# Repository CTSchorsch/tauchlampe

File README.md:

# tauchlampe

10W LED Tanklampe mit Goodmanhandle

Version 4.2
- neues PCB, einseitig, liegt direkt auf der LED-Aufnahme auf, JST Stecker für Taster und Power
- Abdeckung für PCB
- LED-Aufnahme für Produktion vereinfacht
- Deckel für Akkufach: 2 Bananenbuchsen zum laden, Durchführung für JST Kabel

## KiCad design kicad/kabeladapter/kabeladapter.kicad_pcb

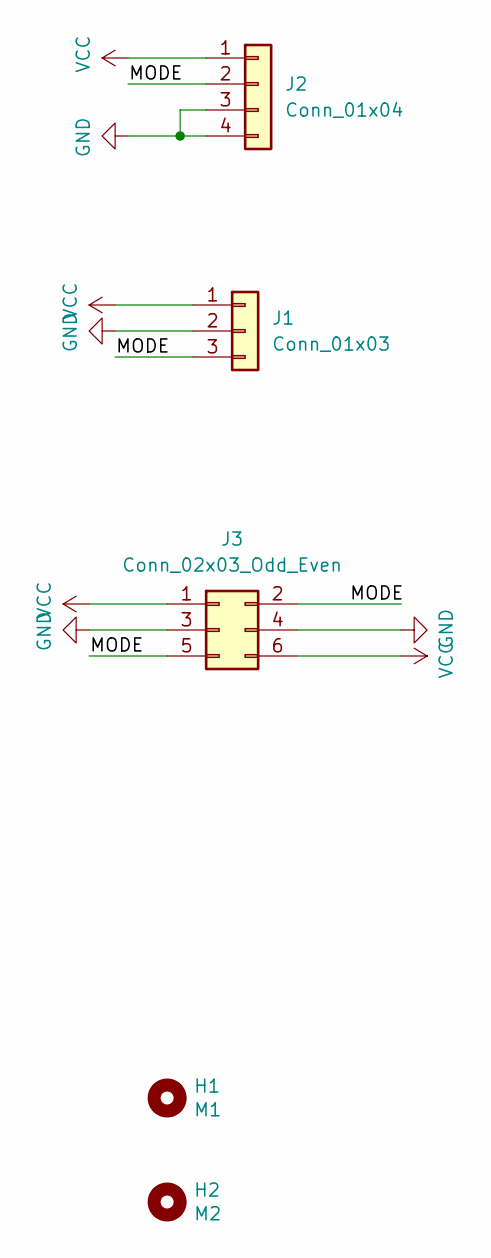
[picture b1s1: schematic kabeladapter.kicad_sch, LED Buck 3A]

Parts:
H1: M1; MountingHole_3.2mm_M3
H2: M2; MountingHole_3.2mm_M3
J1: Conn_01x03; JST_PH_B3B-PH-SM4-TB_1x03-1MP_P2.00mm_Vertical
J2: Conn_01x04; JST_GH_BM04B-GHS-TBT_1x04-1MP_P1.25mm_Vertical
J3: Conn_02x03_Odd_Even; PinHeader_2x03_P2.00mm_Vertical_SMD

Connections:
/MODE: J1.3, J2.2, J3.2, J3.5
GND: J1.2, J2.3, J2.4, J3.3, J3.4
VCC: J1.1, J2.1, J3.1, J3.6

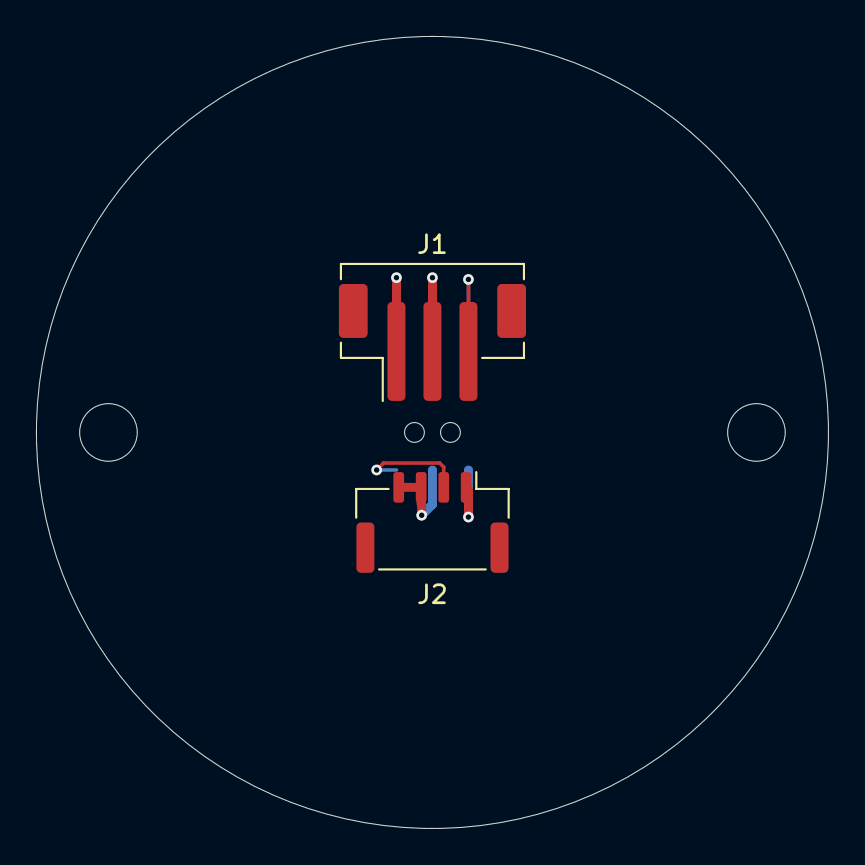
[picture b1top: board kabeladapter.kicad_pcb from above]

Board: 2 copper layers, 44.0 x 44.0 mm, 5 parts (1 on the bottom side), 3 nets.

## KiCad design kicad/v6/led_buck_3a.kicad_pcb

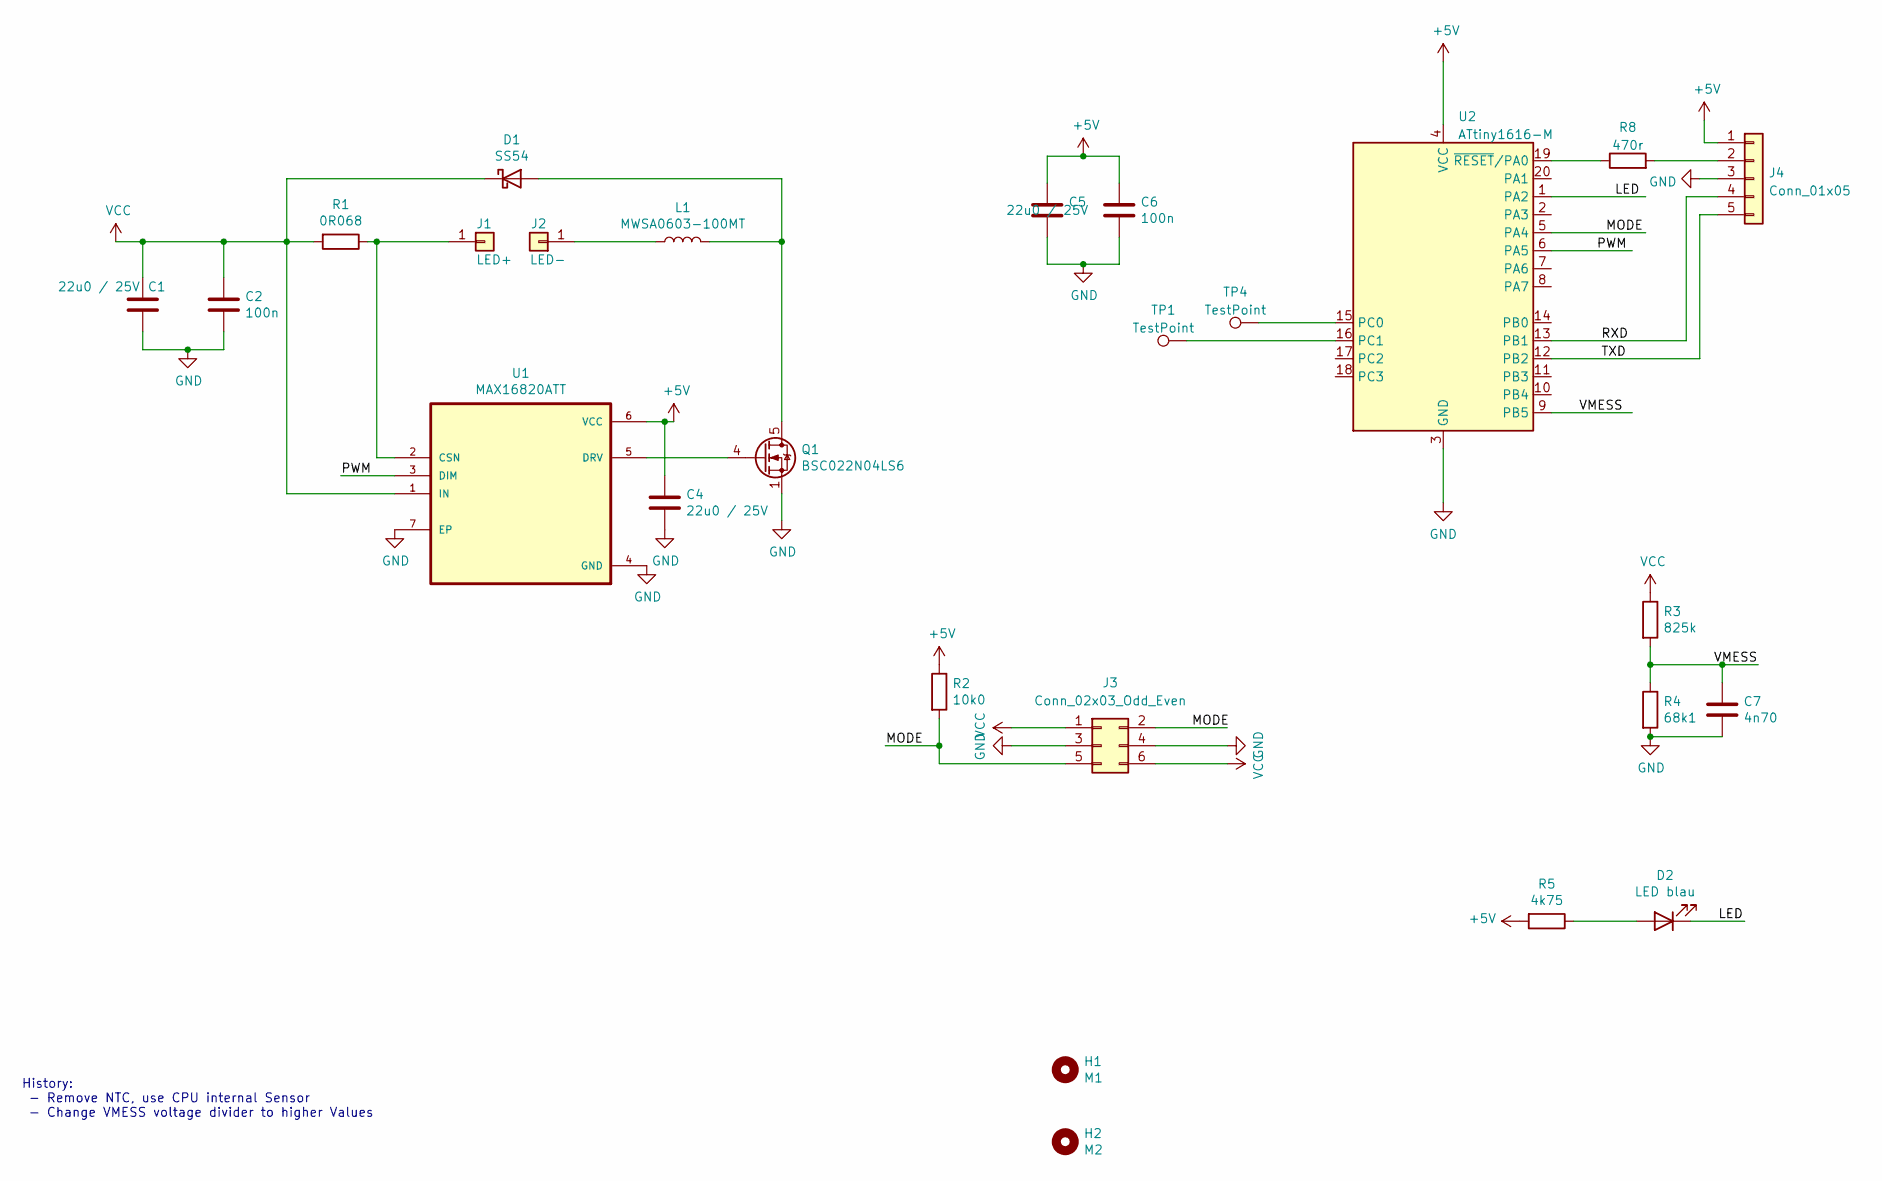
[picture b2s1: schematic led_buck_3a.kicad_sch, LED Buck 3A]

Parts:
C1, C4, C5: 22u0 / 25V; C_0805_2012Metric; LCSC C45783
C2, C6: 100n; C_0805_2012Metric; LCSC C49678
C7: 4n70; C_0805_2012Metric; LCSC C1744
D1: SS54; D_SMA; LCSC C22452
D2: LED blau; LED_0805_2012Metric; LCSC C2293
H1: M1; MountingHole_3.2mm_M3
H2: M2; MountingHole_3.2mm_M3
J1: LED+; TestPoint_Plated_Hole_D3.0mm
J2: LED-; TestPoint_Plated_Hole_D3.0mm
J3: Conn_02x03_Odd_Even; PinHeader_2x03_P2.00mm_Vertical_SMD
J4: Conn_01x05; PinHeader_1x05_P2.00mm_Vertical
L1: MWSA0603-100MT; L_Sumida_CDMC6D28_7.25x6.5mm; LCSC C132141
Q1: BSC022N04LS6; TDSON-8-1; LCSC C534307
R1: 0R068; R_2512_6332Metric; LCSC C534307
R2: 10k0; R_0805_2012Metric; LCSC C17414
R3: 825k; R_0805_2012Metric; LCSC C17835
R4: 68k1; R_0805_2012Metric; LCSC C17771
R5: 4k75; R_0805_2012Metric; LCSC C17672
R8: 470r; R_0805_2012Metric
TP1, TP4: TestPoint; TestPoint_Pad_1.0x1.0mm
U1: MAX16820ATT; SON95P300X300X80-7N; LCSC C143371
U2: ATtiny1616-M; VQFN-20-1EP_3x3mm_P0.4mm_EP1.7x1.7mm

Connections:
+5V: C4.1, C5.1, C6.1, J4.1, R2.1, R5.2, U1.6 (VCC), U2.4 (VCC)
/LED: D2.1 (K), U2.1 (PA2)
/MODE: J3.2, J3.5, R2.2, U2.5 (PA4)
/PWM: U1.3 (DIM), U2.6 (PA5)
/RXD: J4.4, U2.13 (PB1)
/TXD: J4.5, U2.12 (PB2)
/VMESS: C7.1, R3.2, R4.1, U2.9 (PB5)
GND: C1.2, C2.2, C4.2, C5.2, C6.2, C7.2, J3.3, J3.4, J4.3, Q1.1 (S), Q1.2 (S), Q1.3 (S), R4.2, U1.4 (GND), U1.7 (EP), U2.3 (GND), U2.21 (GND)
unnamed: D1.2 (A), L1.2, Q1.5 (D)
unnamed: D2.2 (A), R5.1
unnamed: J1.1, R1.1, U1.2 (CSN)
unnamed: J2.1, L1.1
unnamed: J4.2, R8.2
unnamed: Q1.4 (G), U1.5 (DRV)
unnamed: TP4.1, U2.15 (PC0)
unnamed: TP1.1, U2.16 (PC1)
unnamed: R8.1, U2.19 (~RESET/PA0)
VCC: C1.1, C2.1, D1.1 (K), J3.1, J3.6, R1.2, R3.1, U1.1 (IN)

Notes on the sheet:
History: - Remove NTC, use CPU internal Sensor - Change VMESS voltage divider to higher Values

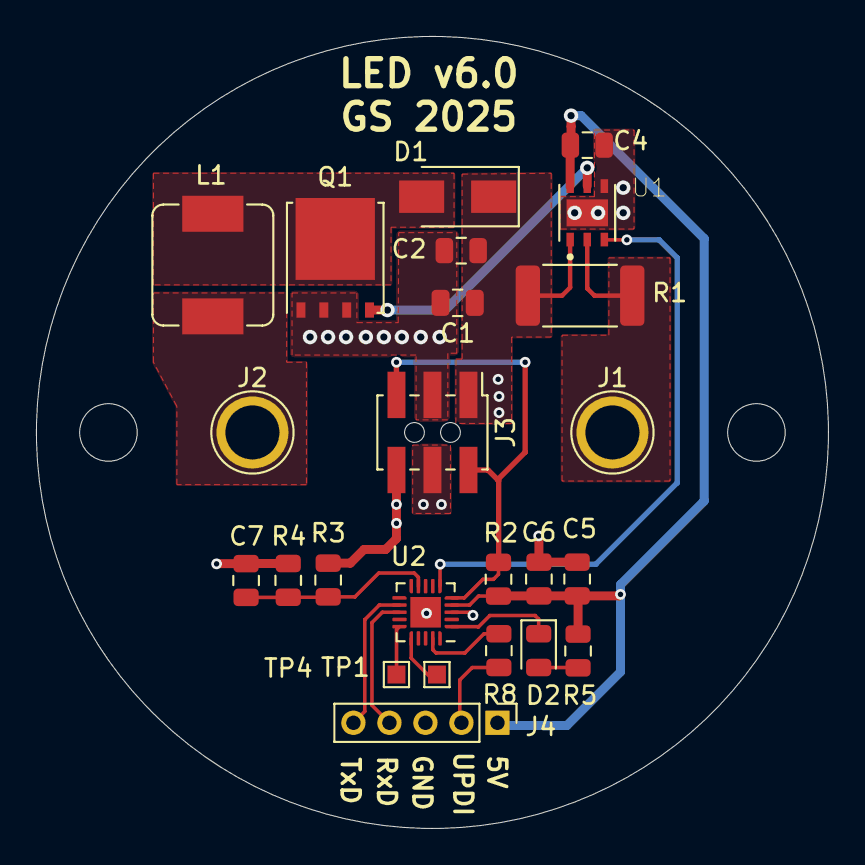
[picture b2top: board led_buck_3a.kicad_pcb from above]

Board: 2 copper layers, 44.0 x 44.0 mm, 26 parts (0 on the bottom side), 18 nets.

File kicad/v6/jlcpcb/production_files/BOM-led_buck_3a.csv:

Comment,Designator,Footprint,LCSC,Quantity
MWSA0603-100MT,L1,L_Sumida_CDMC6D28_7.25x6.5mm,C132141,1
MAX16820ATT,U1,SON95P300X300X80-7N,C143371,1
10k0,R2,R_0805_2012Metric,C17414,1
4n70,C7,C_0805_2012Metric,C1744,1
4k75,R5,R_0805_2012Metric,C17672,1
68k1,R4,R_0805_2012Metric,C17771,1
825k,R3,R_0805_2012Metric,C17835,1
SS54,D1,D_SMA,C22452,1
LED blau,D2,LED_0805_2012Metric,C2293,1
22u0 / 25V,"C4,C5",C_0805_2012Metric,C45783,2
100n,"C2,C6",C_0805_2012Metric,C49678,2
0R070,R1,R_2512_6332Metric,C76251,1
22u0 / 25V,C1,C_0805_2012Metric,C90143,1
Conn_02x03_Odd_Even,J3,PinHeader_2x03_P2.00mm_Vertical_SMD,,1
ATtiny1616-M,U2,VQFN-20-1EP_3x3mm_P0.4mm_EP1.7x1.7mm,,1
M1,H1,MountingHole_3.2mm_M3,,1
M2,H2,MountingHole_3.2mm_M3,,1
BSC022N04LSATMA,Q1,TDSON-8-1,,1
470r,R8,R_0805_2012Metric,,1
TestPoint,TP1,TestPoint_Pad_1.0x1.0mm,,1
Conn_01x05,J4,PinHeader_1x05_P2.00mm_Vertical,,1
TestPoint,TP4,TestPoint_Pad_1.0x1.0mm,,1
LED+,J1,TestPoint_Plated_Hole_D3.0mm,,1
LED-,J2,TestPoint_Plated_Hole_D3.0mm,,1

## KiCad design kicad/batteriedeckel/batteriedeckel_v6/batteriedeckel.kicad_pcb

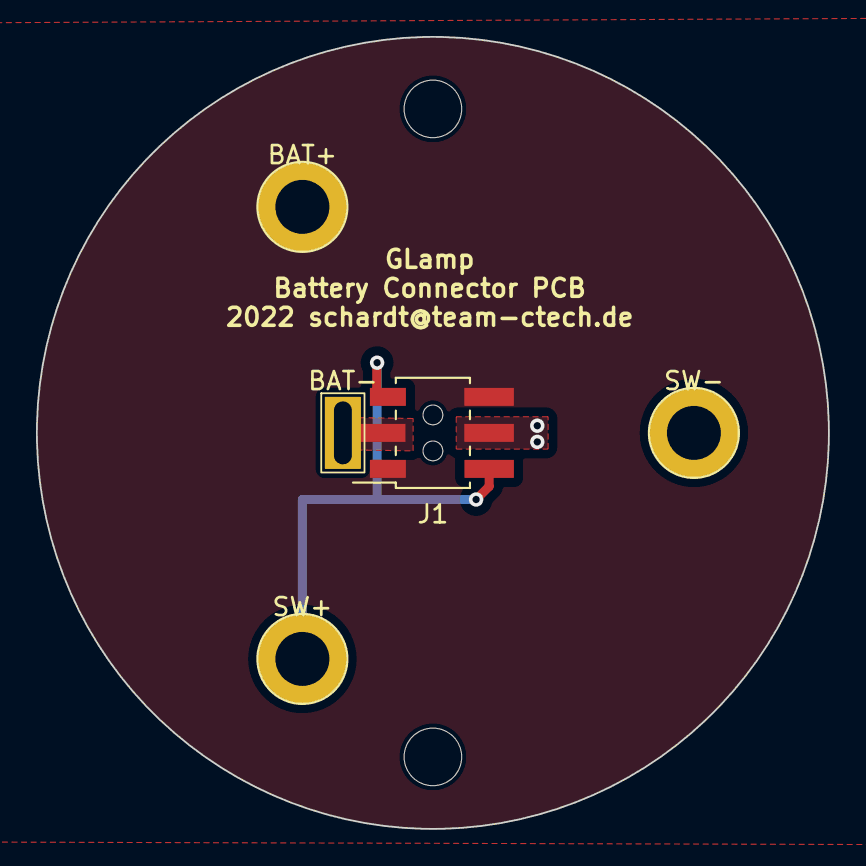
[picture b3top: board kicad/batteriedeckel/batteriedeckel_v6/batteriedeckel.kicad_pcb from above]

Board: 2 copper layers, 44.0 x 44.0 mm, 7 parts (0 on the bottom side), 3 nets.

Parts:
BAT+: BAT+; TestPoint_THTPad_D5.0mm_Drill3.0mm
BAT-: BAT-; TestPoint_THTPad_D5.0mm_Drill3.0mm
H1, H2: MountingHole; MountingHole_3.2mm_M3_DIN965
J1: Conn_02x03_Odd_Even; PinSocket_2x03_P2.00mm_Vertical_SMD
SW+: SW+; TestPoint_THTPad_D5.0mm_Drill3.0mm
SW-: SW-; TestPoint_THTPad_D5.0mm_Drill3.0mm

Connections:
/BAT+: BAT+.1, J1.1, J1.6
/GND: BAT-.1, J1.3, J1.4, SW-.1
/MODE: J1.2, J1.5, SW+.1

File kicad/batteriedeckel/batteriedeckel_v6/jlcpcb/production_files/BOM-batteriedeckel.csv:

Comment,Designator,Footprint,LCSC,Quantity
Conn_02x03_Odd_Even,J1,PinSocket_2x03_P2.00mm_Vertical_SMD,,1
MountingHole,H2,MountingHole_3.2mm_M3_DIN965,,1
MountingHole,H1,MountingHole_3.2mm_M3_DIN965,,1

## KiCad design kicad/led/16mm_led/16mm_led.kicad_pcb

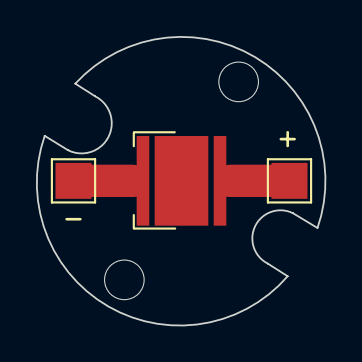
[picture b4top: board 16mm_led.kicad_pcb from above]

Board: 2 copper layers, 16.0 x 16.0 mm, 5 parts (0 on the bottom side), 2 nets.

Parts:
D1: LED; LED_Cree-XM
H1, H2: MountingHole; MountingHole_2.2mm_M2
TP1: -; TestPoint_Pad_2.0x2.0mm
TP2: +; TestPoint_Pad_2.0x2.0mm

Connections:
unnamed: D1.1 (K), TP1.1
unnamed: D1.2 (A), TP2.1

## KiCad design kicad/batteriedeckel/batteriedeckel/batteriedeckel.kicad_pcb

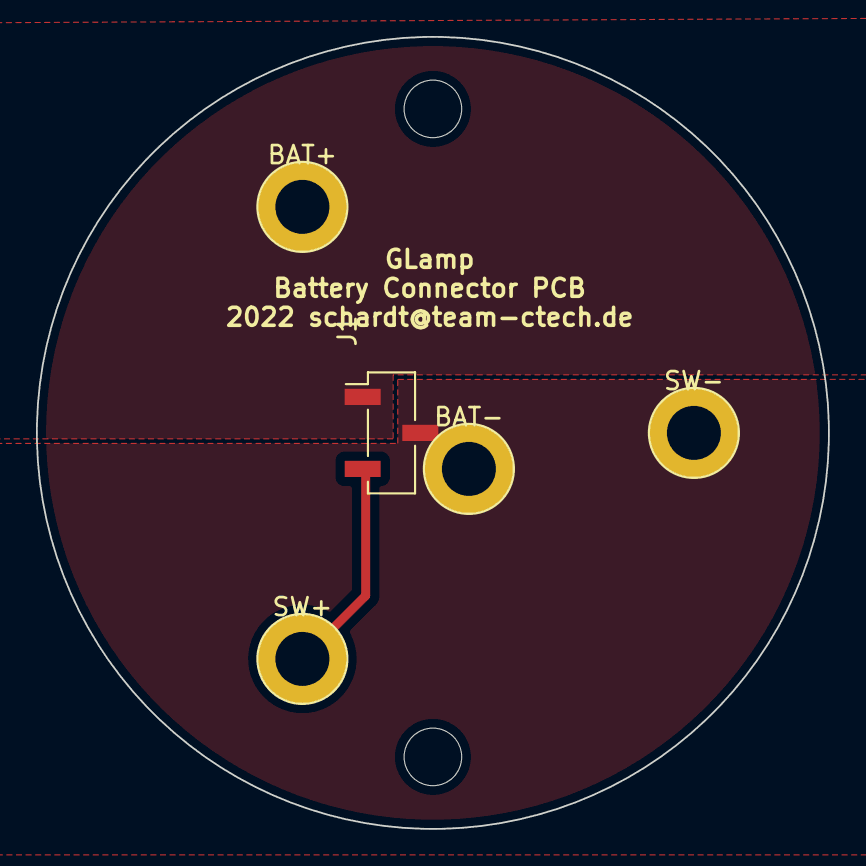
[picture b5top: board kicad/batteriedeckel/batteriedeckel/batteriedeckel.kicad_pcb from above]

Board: 2 copper layers, 44.0 x 44.0 mm, 7 parts (0 on the bottom side), 3 nets.

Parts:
BAT+: BAT+; TestPoint_THTPad_D5.0mm_Drill3.0mm
BAT-: BAT-; TestPoint_THTPad_D5.0mm_Drill3.0mm
H1, H2: MountingHole; MountingHole_3.2mm_M3_DIN965
J1: Conn_01x03; PinSocket_1x03_P2.00mm_Vertical_SMD_Pin1Left
SW+: SW+; TestPoint_THTPad_D5.0mm_Drill3.0mm
SW-: SW-; TestPoint_THTPad_D5.0mm_Drill3.0mm

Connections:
/BAT+: BAT+.1, J1.1
/GND: BAT-.1, J1.2, SW-.1
/MODE: J1.3, SW+.1

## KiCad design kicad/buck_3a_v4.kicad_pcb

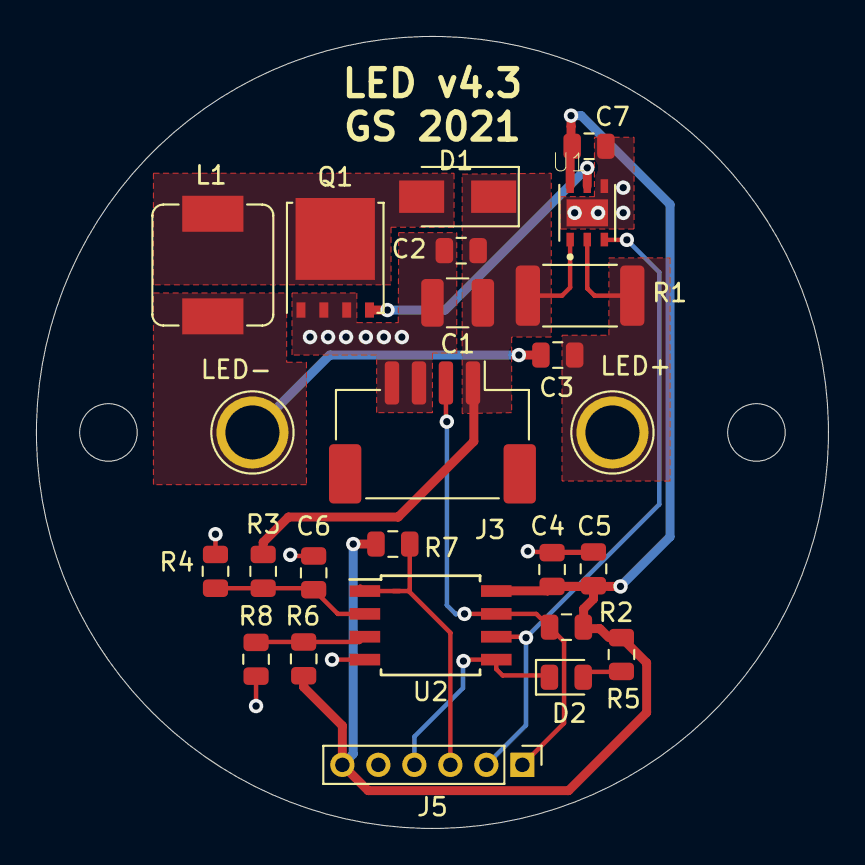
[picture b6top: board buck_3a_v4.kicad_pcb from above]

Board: 2 copper layers, 44.0 x 44.0 mm, 27 parts (0 on the bottom side), 14 nets.

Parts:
C1: 100u/16V; C_1210_3225Metric
C2, C5: 100n; C_0805_2012Metric
C3: DNP; C_0805_2012Metric
C4, C7: 22u0/16V; C_0805_2012Metric
C6: 4n70; C_0805_2012Metric
D1: SS54; D_SMA
D2: LED blau; LED_0805_2012Metric
H1: M1; MountingHole_3.2mm_M3
H2: M2; MountingHole_3.2mm_M3
J3: Conn_01x04; JST_ZE_BM04B-ZESS-TBT_1x04-1MP_P1.50mm_Vertical
J5: Conn_01x06; PinHeader_1x06_P2.00mm_Vertical
L1: MWSA0603-100MT; L_Sumida_CDMC6D28_7.25x6.5mm
LED+: LED+; TestPoint_Plated_Hole_D3.0mm
LED-: LED-; TestPoint_Plated_Hole_D3.0mm
Q1: BSC022N04LSATMA; TDSON-8-1
R1: 0R070; R_2512_6332Metric
R2, R6, R7: 10k0; R_0805_2012Metric
R3: 82k5; R_0805_2012Metric
R4: 6k81; R_0805_2012Metric
R5: 4k75; R_0805_2012Metric
R8: CMFB103F3950FANT; R_0805_2012Metric
U1: MAX16820ATT; SON95P300X300X80-7N
U2: ATtiny45-20SU; SOIJ-8_5.3x5.3mm_P1.27mm

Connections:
+5V: C4.1, C5.1, C7.1, J5.6, R2.1, R5.2, R6.1, R7.1, U1.6, U2.8
/LED: D2.1, J5.4, U2.5
/MODE: J3.2, J5.1, R2.2, U2.7
/PWM: J5.2, U1.3, U2.6
/RESET: J5.3, R7.2, U2.1
/TMESS: R6.2, R8.1, U2.3
/VMESS: C6.1, R3.2, R4.1, U2.2
GND: C1.2, C2.2, C4.2, C5.2, C6.2, C7.2, J3.3, J3.4, J5.5, Q1.1, Q1.2, Q1.3, R4.2, R8.2, U1.4, U1.7, U2.4
unnamed: C3.1, L1.1, LED-.1
unnamed: C3.2, LED+.1, R1.1, U1.2
unnamed: D1.2, L1.2, Q1.5
unnamed: D2.2, R5.1
unnamed: Q1.4, U1.5
VCC: C1.1, C2.1, D1.1, J3.1, R1.2, R3.1, U1.1

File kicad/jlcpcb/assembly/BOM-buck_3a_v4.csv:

Comment,Designator,Footprint,LCSC
MWSA0603-100MT,L1,L_Sumida_CDMC6D28_7.25x6.5mm,C132141
BSC022N04LSATMA,Q1,TDSON-8-1,C148266
100u/16V,C1,C_1210_3225Metric,C15850
10k0,"R2,R6,R7",R_0805_2012Metric,C17414
4n70,C6,C_0805_2012Metric,C1744
4k75,R5,R_0805_2012Metric,C17673
6k81,R4,R_0805_2012Metric,C17772
82k5,R3,R_0805_2012Metric,C17840
SS54,D1,D_SMA,C22452
LED blau,D2,LED_0805_2012Metric,C2286
MAX16820ATT,U1,SON95P300X300X80-7N,C2678567
100n,"C2,C5",C_0805_2012Metric,C49678
22u0/16V,"C4,C7",C_0805_2012Metric,C602037
ATtiny45-20SU,U2,SOIJ-8_5.3x5.3mm_P1.27mm,C62689
0R070,R1,R_2512_6332Metric,C76251
CMFB103F3950FANT,R8,R_0805_2012Metric,C95968

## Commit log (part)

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2020-11-12 Frisch aufgeräumt
2020-11-13 Zeichnung fertig gestellt Aufbau Dokument begonnen
2020-11-13 Explosionszeichnung neu O-Ringe hinzugefügt
2020-11-13 STLs für 3D Druckteile hinzugefügt
2020-11-17 uc_src angepasst
2020-12-01 change some parts to non-china parts add some gnd vias to JST connector add new chapter to Aufbau.pdf port uc firmware to new Uc
2021-01-17 Fix sleep mode with battery pack
2021-01-31 save
2021-04-06 bugfix sleep mode
2021-04-15 bugifx
2021-04-16 mech/ Lampengehäuse getauscht zu Variante mit O-Ring
    kicad/
    Neue Version mit besserem Layout
    Neue JLC Daten
2021-05-04 3A Regler V4 tested with JLC Parts
2021-10-25 main.c: add sleep_bod_disable()
2022-09-15 Save V4.3
2022-09-19 change kicad folder
2022-10-26 Software v5
2024-01-10 - Neues PCB V5.1 - Ädernungen an den Akkufach 3D Teilen - Firmware überarbeitet
2024-01-10 Schaltplan vergessen
2024-01-10 Neue Mechanik hinterlegt
2025-10-24 clean up
